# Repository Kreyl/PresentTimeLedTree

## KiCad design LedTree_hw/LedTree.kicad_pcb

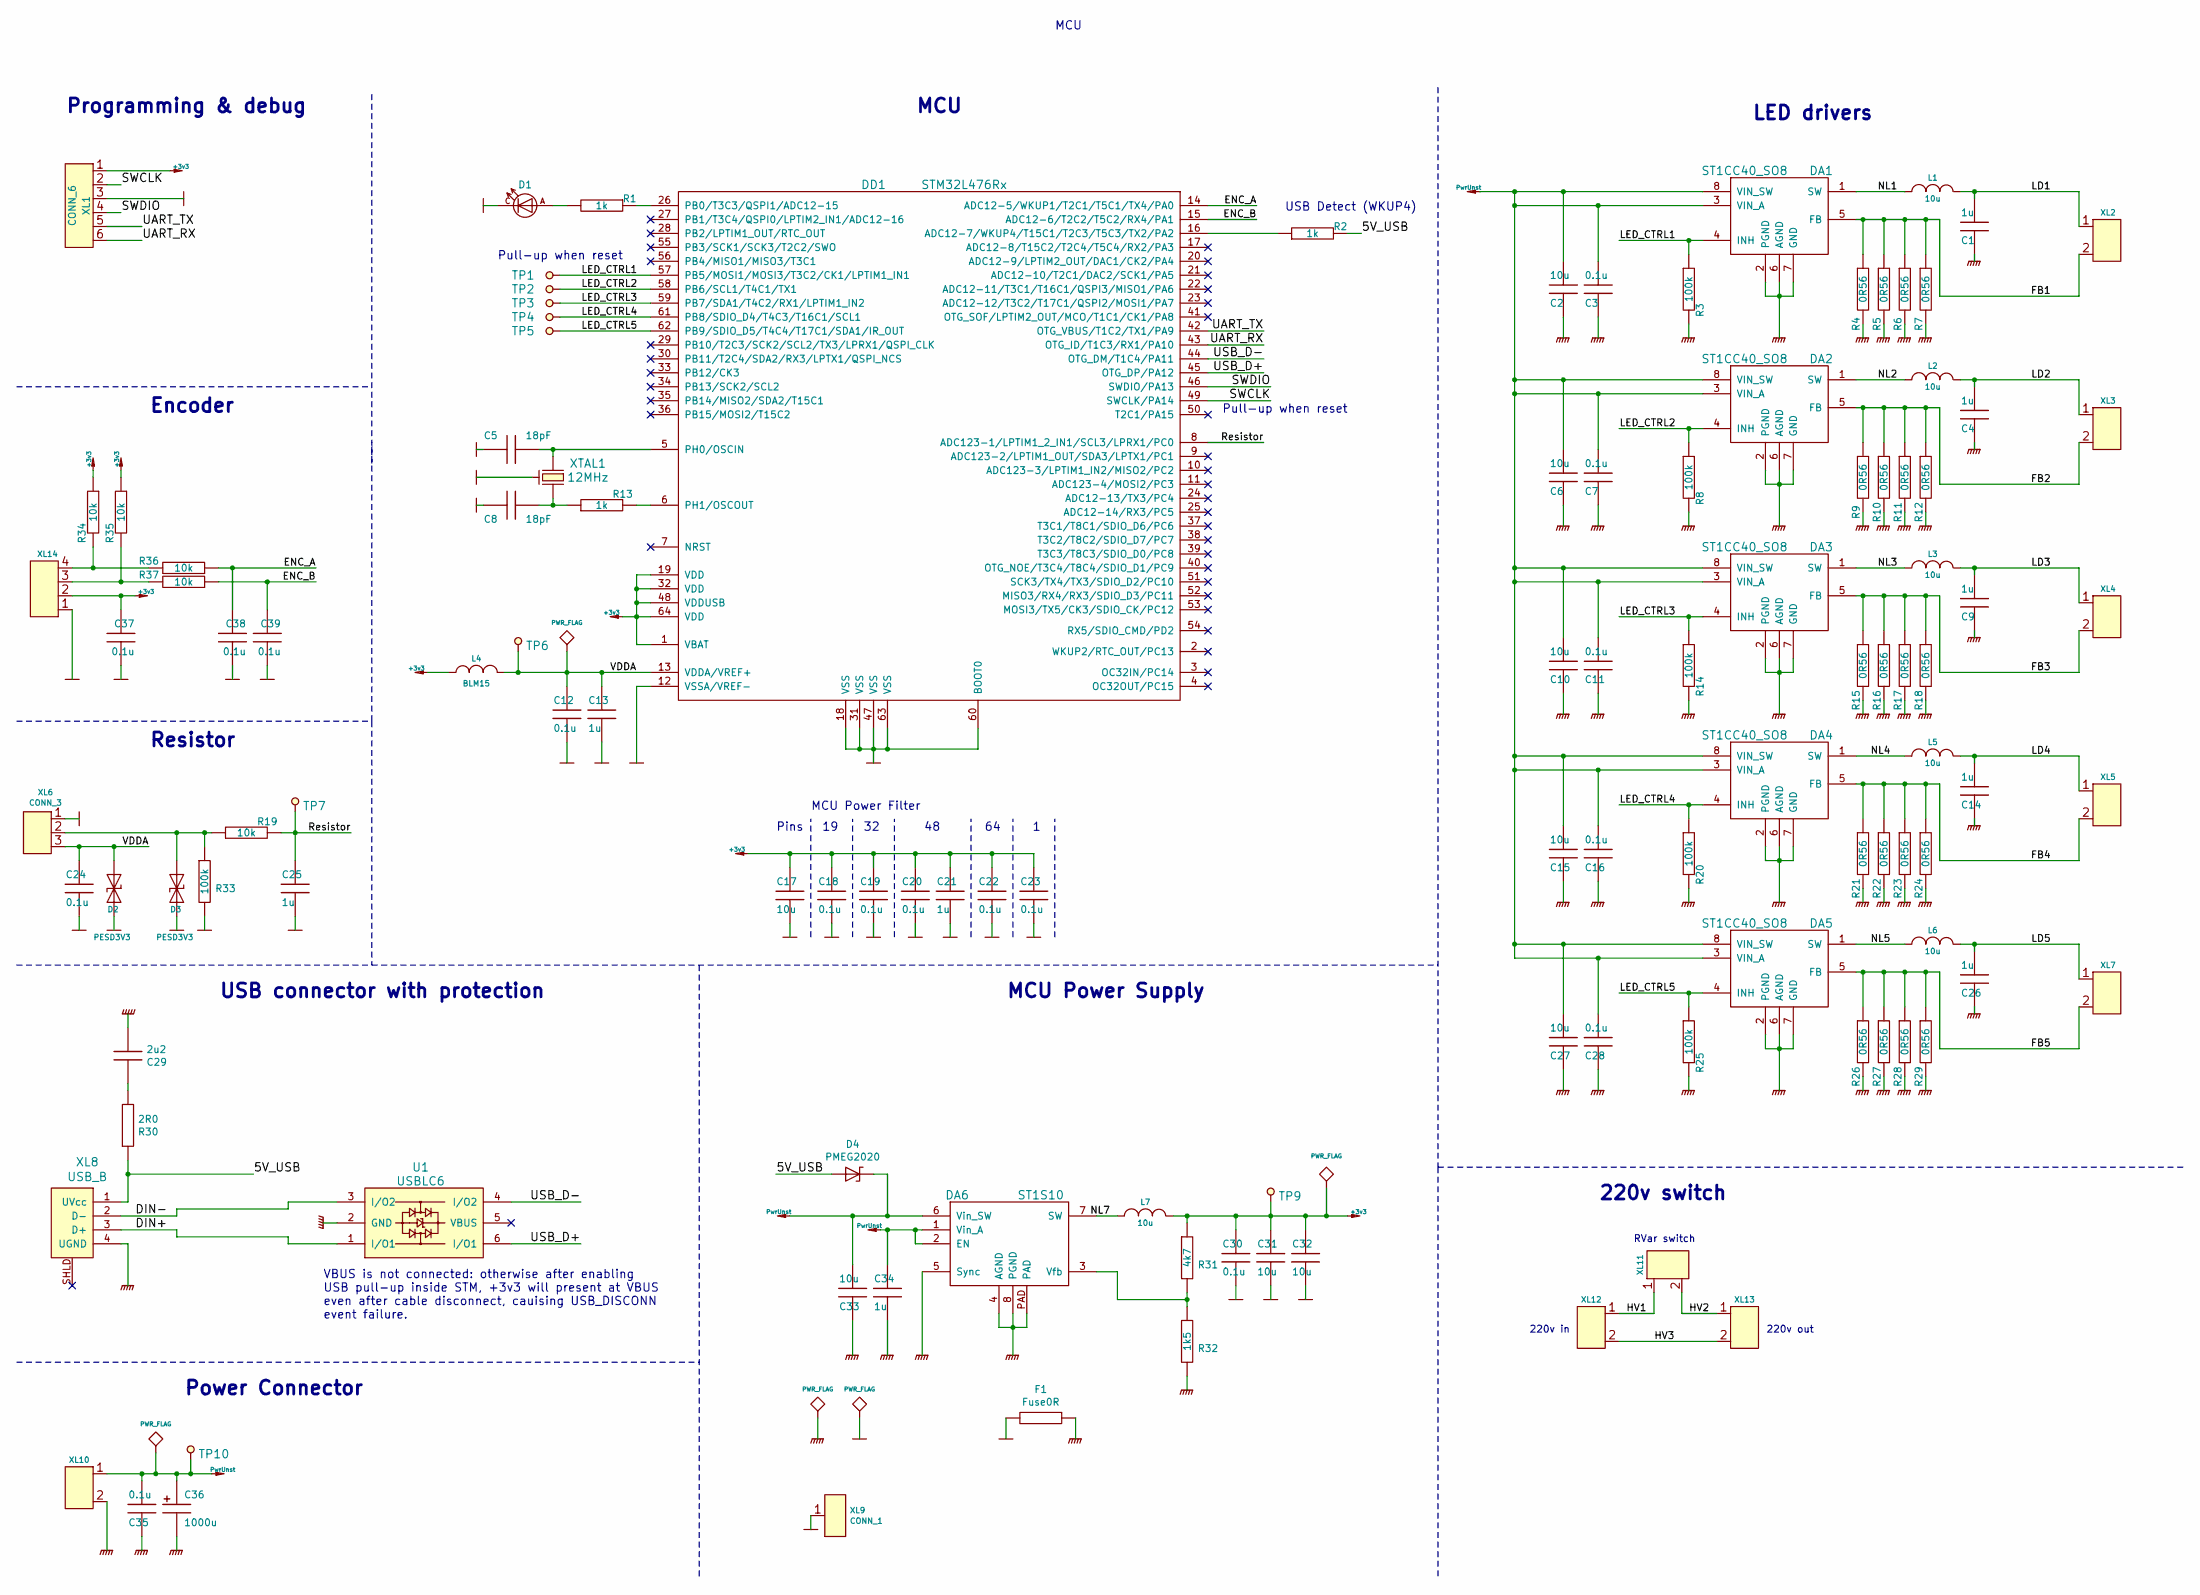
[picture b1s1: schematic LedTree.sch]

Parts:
C1, C4, C9, C14, C26, C34: 1u; CAP_0603_Silks
C2, C6, C10, C15, C27, C33: 10u; CAP_0805
C3, C7, C11, C16, C28, C30, C35: 0.1u; CAP_0603_Silks
C5, C8: 18pF; CAP_0603
C12, C18, C19, C20, C22, C23, C24, C37, C38, C39: 0.1u; CAP_0603
C13, C21, C25: 1u; CAP_0603
C17: 10u; CAP_0603
C29: 2u2; CAP_0603_Silks
C31, C32: 10u; CAP_0603_Silks
C36: 1000u; CAP_10xxR
D1: LED; LED_0603
D2, D3: PESD3V3; SOD323
D4: PMEG2020; SOD323
DA1, DA2, DA3, DA4, DA5: ST1CC40_SO8; SO8_150MIL
DA6: ST1S10; SO8HEATSINK
DD1: STM32L476Rx; LQFP64
F1: Fuse0R; FuseShorted
L1, L2, L3, L5, L6, L7: 10u; SDR0604
L4: BLM15; IND_0402
R1, R2, R13: 1k; RES_0603
R3, R8, R14, R20, R25, R33: 100k; RES_0603
R4, R5, R6, R7, R9, R10, R11, R12, R15, R16, R17, R18, R21, R22, R23, R24, R26, R27, R28, R29: 0R56; RES_0805
R19, R34, R35, R36, R37: 10k; RES_0603
R30: 2R0; RES_0603
R31: 4k7; RES_0603
R32: 1k5; RES_0603
TP1, TP2, TP3, TP4, TP5, TP6, TP7, TP9, TP10: TESTPOINT; TESTPOINT_1MM
U1: USBLC6; SOT23-6
XL1: CONN_6; PLS-6_LOCK
XL2, XL3, XL4, XL5, XL7, XL10, XL12, XL13: CONN_2; XY122V-2
XL6: CONN_3; WB-03(MW-3M)
XL8: USB_B; USB_B_Vertical_1JF
XL9: CONN_1; PLS-1Rnd
XL11: CONN_2; W02_Pitch_2d54
XL14: CONN_4; WB-04(MW-4M)
XTAL1: 12MHz; 03225C4

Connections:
+3v3: C17.2, C18.2, C19.2, C20.2, C21.2, C22.2, C23.2, C30.2, C31.2, C32.2, C37.2, DD1.1 (VBAT), DD1.19 (VDD), DD1.32 (VDD), DD1.48 (VDDUSB), DD1.64 (VDD), L4.1, L7.1, R31.1, R34.1, R35.1, TP9.1, XL1.1, XL14.2 (PM)
/5V_USB: D4.A, R2.2, R30.1, XL8.1 (UVcc)
/DIN+: U1.1 (I/O1), XL8.3 (D+)
/DIN-: U1.3 (I/O2), XL8.2 (D-)
/ENC_A: C38.2, DD1.14 (ADC12-5/WKUP1/T2C1/T5C1/TX4/PA0), R36.1
/ENC_B: C39.2, DD1.15 (ADC12-6/T2C2/T5C2/RX4/PA1), R37.1
/FB1: DA1.5 (FB), R4.1, R5.1, R6.1, R7.1, XL2.2 (PM)
/FB2: DA2.5 (FB), R9.1, R10.1, R11.1, R12.1, XL3.2 (PM)
/FB3: DA3.5 (FB), R15.1, R16.1, R17.1, R18.1, XL4.2 (PM)
/FB4: DA4.5 (FB), R21.1, R22.1, R23.1, R24.1, XL5.2 (PM)
/FB5: DA5.5 (FB), R26.1, R27.1, R28.1, R29.1, XL7.2 (PM)
/HV1: XL11.1, XL12.1
/HV2: XL11.2 (PM), XL13.1
/HV3: XL12.2 (PM), XL13.2 (PM)
/LD1: C1.1, L1.1, XL2.1
/LD2: C4.1, L2.1, XL3.1
/LD3: C9.1, L3.1, XL4.1
/LD4: C14.1, L5.1, XL5.1
/LD5: C26.1, L6.1, XL7.1
/LED_CTRL1: DA1.4 (INH), DD1.57 (PB5/MOSI1/MOSI3/T3C2/CK1/LPTIM1_IN1), R3.1, TP1.1
/LED_CTRL2: DA2.4 (INH), DD1.58 (PB6/SCL1/T4C1/TX1), R8.1, TP2.1
/LED_CTRL3: DA3.4 (INH), DD1.59 (PB7/SDA1/T4C2/RX1/LPTIM1_IN2), R14.1, TP3.1
/LED_CTRL4: DA4.4 (INH), DD1.61 (PB8/SDIO_D4/T4C3/T16C1/SCL1), R20.1, TP4.1
/LED_CTRL5: DA5.4 (INH), DD1.62 (PB9/SDIO_D5/T4C4/T17C1/SDA1/IR_OUT), R25.1, TP5.1
/NL1: DA1.1 (SW), L1.2
/NL2: DA2.1 (SW), L2.2
/NL3: DA3.1 (SW), L3.2
/NL4: DA4.1 (SW), L5.2
/NL5: DA5.1 (SW), L6.2
/NL7: DA6.7 (SW), L7.2
/Resistor: C25.2, DD1.8 (ADC123-1/LPTIM1_2_IN1/SCL3/LPRX1/PC0), R19.2, TP7.1
/SWCLK: DD1.49 (SWCLK/PA14), XL1.2
/SWDIO: DD1.46 (SWDIO/PA13), XL1.4
/UART_RX: DD1.43 (OTG_ID/T1C3/RX1/PA10), XL1.6
/UART_TX: DD1.42 (OTG_VBUS/T1C2/TX1/PA9), XL1.5
/USB_D+: DD1.45 (OTG_DP/PA12), U1.6 (I/O1)
/USB_D-: DD1.44 (OTG_DM/T1C4/PA11), U1.4 (I/O2)
/VDDA: C12.2, C13.2, C24.2, D2.C, DD1.13 (VDDA/VREF+), L4.2, TP6.1, XL6.3
GND: C5.2, C8.2, C12.1, C13.1, C17.1, C18.1, C19.1, C20.1, C21.1, C22.1, C23.1, C24.1, C25.1, C30.1, C31.1, C32.1, C37.1, C38.1, C39.1, D1.C, D2.A, D3.A, DD1.12 (VSSA/VREF-), DD1.18 (VSS), DD1.31 (VSS), DD1.47 (VSS), DD1.60 (BOOT0), DD1.63 (VSS), F1.2, R33.2, XL1.3, XL6.1, XL9.1, XL14.1, XTAL1.H
GNDPWR: C1.2, C2.2, C3.2, C4.2, C6.2, C7.2, C9.2, C10.2, C11.2, C14.2, C15.2, C16.2, C26.2, C27.2, C28.2, C29.2, C33.2, C34.1, C35.2, C36.2, DA1.2 (PGND), DA1.6 (AGND), DA1.7 (GND), DA2.2 (PGND), DA2.6 (AGND), DA2.7 (GND), DA3.2 (PGND), DA3.6 (AGND), DA3.7 (GND), DA4.2 (PGND), DA4.6 (AGND), DA4.7 (GND), DA5.2 (PGND), DA5.6 (AGND), DA5.7 (GND), DA6.4 (AGND), DA6.5 (Sync), DA6.8 (PGND), DA6.PAD, F1.1, R3.2, R4.2, R5.2, R6.2, R7.2, R8.2, R9.2, R10.2, R11.2, R12.2, R14.2, R15.2, R16.2, R17.2, R18.2, R20.2, R21.2, R22.2, R23.2, R24.2, R25.2, R26.2, R27.2, R28.2, R29.2, R32.2, U1.2 (GND), XL8.4 (UGND), XL10.2 (PM)
unnamed: C5.1, DD1.5 (PH0/OSCIN), XTAL1.1
unnamed: C8.1, R13.1, XTAL1.2
unnamed: C29.1, R30.2
unnamed: D1.A, R1.2
unnamed: D3.C, R19.1, R33.1, XL6.2 (PM)
unnamed: DA6.3 (Vfb), R31.2, R32.1
unnamed: DD1.6 (PH1/OSCOUT), R13.2
unnamed: DD1.16 (ADC12-7/WKUP4/T15C1/T2C3/T5C3/TX2/PA2), R2.1
unnamed: DD1.26 (PB0/T3C3/QSPI1/ADC12-15), R1.1
unnamed: R34.2, R36.2, XL14.4
unnamed: R35.2, R37.2, XL14.3
PwrUnst: C2.1, C3.1, C6.1, C7.1, C10.1, C11.1, C15.1, C16.1, C27.1, C28.1, C33.1, C34.2, C35.1, C36.1, D4.C, DA1.3 (VIN_A), DA1.8 (VIN_SW), DA2.3 (VIN_A), DA2.8 (VIN_SW), DA3.3 (VIN_A), DA3.8 (VIN_SW), DA4.3 (VIN_A), DA4.8 (VIN_SW), DA5.3 (VIN_A), DA5.8 (VIN_SW), DA6.1 (Vin_A), DA6.2 (EN), DA6.6 (Vin_SW), TP10.1, XL10.1

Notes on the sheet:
Programming & debug
Encoder
Resistor
Power Connector
USB connector with protection
VBUS is not connected: otherwise after enabling USB pull-up inside STM, +3v3 will present at VBUS even after cable disconnect, cauising USB_DISCONN event failure.
Pull-up when reset
Pins 19 32 48 64 1
MCU Power Filter
MCU
MCU Power Supply
USB Detect (WKUP4)
220v in
220v switch
RVar switch
LED drivers
220v out

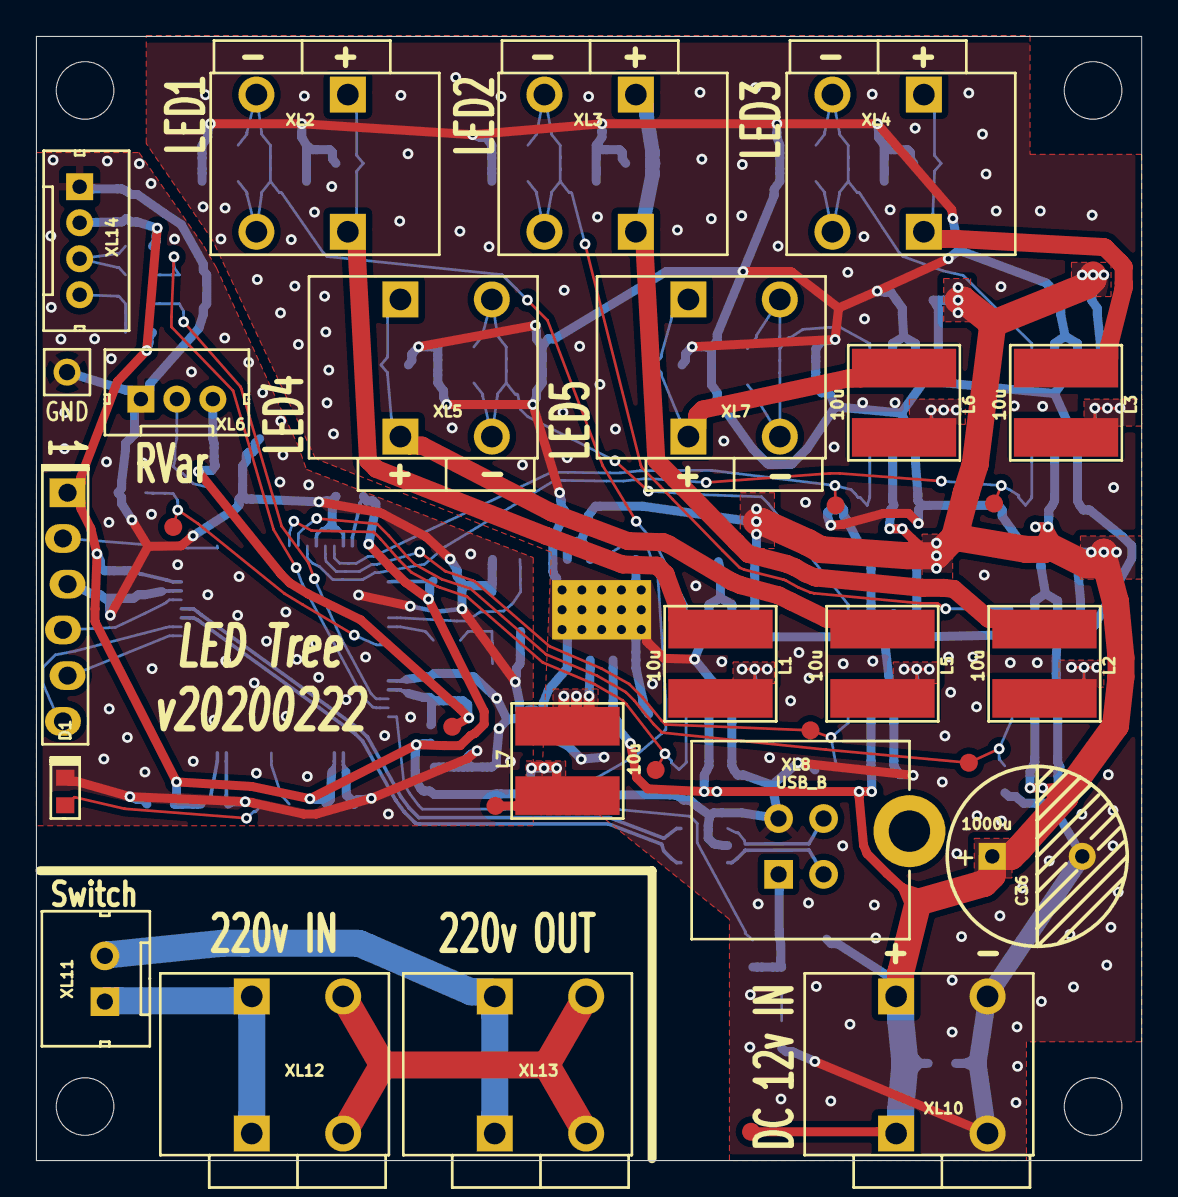
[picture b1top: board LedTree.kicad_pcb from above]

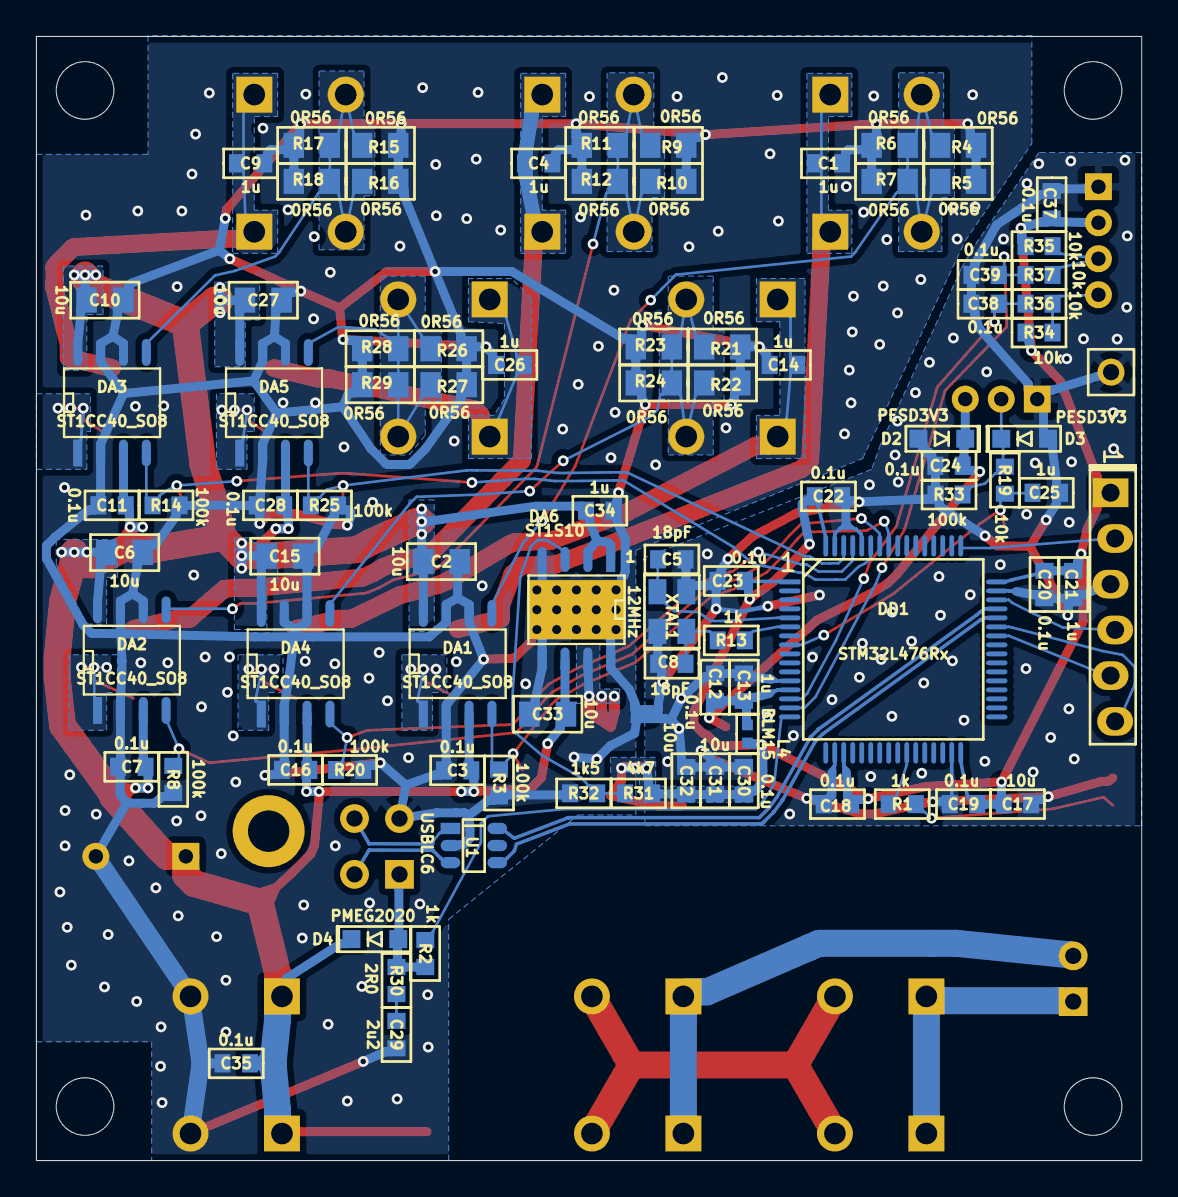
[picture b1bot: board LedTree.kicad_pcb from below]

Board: 2 copper layers, 61.4 x 62.4 mm, 120 parts (90 on the bottom side), 52 nets.

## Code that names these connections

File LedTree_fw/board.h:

/*
 * board.h
 *
 *  Created on: 05 08 2018
 *      Author: Kreyl
 */

#pragma once

// ==== General ====
#define APP_NAME            "LedTree"
#ifndef TRUE
#define TRUE 1
#endif

// MCU type as defined in the ST header.
#define STM32L476xx

// Freq of external crystal if any. Leave it here even if not used.
#define CRYSTAL_FREQ_HZ         12000000

// OS timer settings
#define STM32_ST_IRQ_PRIORITY   2
#define STM32_ST_USE_TIMER      5
#define SYS_TIM_CLK             (Clk.APB1FreqHz)    // Timer 5 is clocked by APB1

//  Periphery
#define SIMPLESENSORS_ENABLED   TRUE

#define ADC_REQUIRED            TRUE
#define STM32_DMA_REQUIRED      TRUE    // Leave this macro name for OS

#if 1 // ========================== GPIO =======================================
// EXTI
#define INDIVIDUAL_EXTI_IRQ_REQUIRED    FALSE

// Encoder
#define ENCA_PIN        GPIOA, 0
#define ENCB_PIN        GPIOA, 1

// Resistor ADC input
#define RESISTOR_PIN    GPIOC, 0, 1 // PC0, ADC channel 1

// UART
#define UART_GPIO       GPIOA
#define UART_TX_PIN     9
#define UART_RX_PIN     10

// LEDs
#define LED_SMOOTH_MAX_BRT      257UL
#define LED_INDICATION  GPIOB, 0, omPushPull
#define LED_MAX_VALUE   (255UL * LED_SMOOTH_MAX_BRT) // Top brightness value
#define LEDS_CNT        5
#define LED1_PIN        { GPIOB, 5, TIM3, 2, invNotInverted, omPushPull, LED_MAX_VALUE }
#define LED2_PIN        { GPIOB, 6, TIM4, 1, invNotInverted, omPushPull, LED_MAX_VALUE }
#define LED3_PIN        { GPIOB, 7, TIM4, 2, invNotInverted, omPushPull, LED_MAX_VALUE }
#define LED4_PIN        { GPIOB, 8, TIM4, 3, invNotInverted, omPushPull, LED_MAX_VALUE }
#define LED5_PIN        { GPIOB, 9, TIM4, 4, invNotInverted, omPushPull, LED_MAX_VALUE }

// USB
#define USB_DM          GPIOA, 11
#define USB_DP          GPIOA, 12
#define USB_AF          AF10
// USB detect
#define USB_DETECT_PIN  GPIOA, 2

#endif // GPIO

#if 1 // =========================== DMA =======================================
// ==== Uart ====
// Remap is made automatically if required
#define UART_DMA_TX     STM32_DMA_STREAM_ID(2, 6)
#define UART_DMA_RX     STM32_DMA_STREAM_ID(2, 7)
#define UART_DMA_CHNL   2
#define UART_DMA_TX_MODE(Chnl) (STM32_DMA_CR_CHSEL(Chnl) | DMA_PRIORITY_LOW | STM32_DMA_CR_MSIZE_BYTE | STM32_DMA_CR_PSIZE_BYTE | STM32_DMA_CR_MINC | STM32_DMA_CR_DIR_M2P | STM32_DMA_CR_TCIE)
#define UART_DMA_RX_MODE(Chnl) (STM32_DMA_CR_CHSEL(Chnl) | DMA_PRIORITY_MEDIUM | STM32_DMA_CR_MSIZE_BYTE | STM32_DMA_CR_PSIZE_BYTE | STM32_DMA_CR_MINC | STM32_DMA_CR_DIR_P2M | STM32_DMA_CR_CIRC)

#if ADC_REQUIRED
#define ADC_DMA         STM32_DMA_STREAM_ID(1, 1)
#define ADC_DMA_MODE    STM32_DMA_CR_CHSEL(0) |   /* DMA1 Stream1 Channel0 */ \
                        DMA_PRIORITY_LOW | \
                        STM32_DMA_CR_MSIZE_HWORD | \
                        STM32_DMA_CR_PSIZE_HWORD | \
                        STM32_DMA_CR_MINC |       /* Memory pointer increase */ \
                        STM32_DMA_CR_DIR_P2M |    /* Direction is peripheral to memory */ \
                        STM32_DMA_CR_TCIE         /* Enable Transmission Complete IRQ */
#endif // ADC

#endif // DMA

#if 1 // ========================== USART ======================================
#define PRINTF_FLOAT_EN TRUE
#define UART_TXBUF_SZ   4096
#define UART_RXBUF_SZ   99

#define UARTS_CNT       1

#define CMD_UART_PARAMS \
    USART1, UART_GPIO, UART_TX_PIN, UART_GPIO, UART_RX_PIN, \
    UART_DMA_TX, UART_DMA_RX, UART_DMA_TX_MODE(UART_DMA_CHNL), UART_DMA_RX_MODE(UART_DMA_CHNL), \
    uartclkHSI // Use independent clock

#endif

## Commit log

2020-02-15 Sch seems done
2020-02-22 + PCB is ready
2020-02-28 +MCU works, LED blinks
2020-02-29 + USB MSD
2020-03-01 ADC works as intended, but with lots of debug
2020-03-01 ADC code clen-up
2020-03-01 + Led with brightness. Works ok.
2020-03-05 + Filesys
2020-03-07 Profile is trapetia
2020-03-09 Algo seems working
2020-03-09 + config Usb does not work
2020-03-09 Release + BootL476
